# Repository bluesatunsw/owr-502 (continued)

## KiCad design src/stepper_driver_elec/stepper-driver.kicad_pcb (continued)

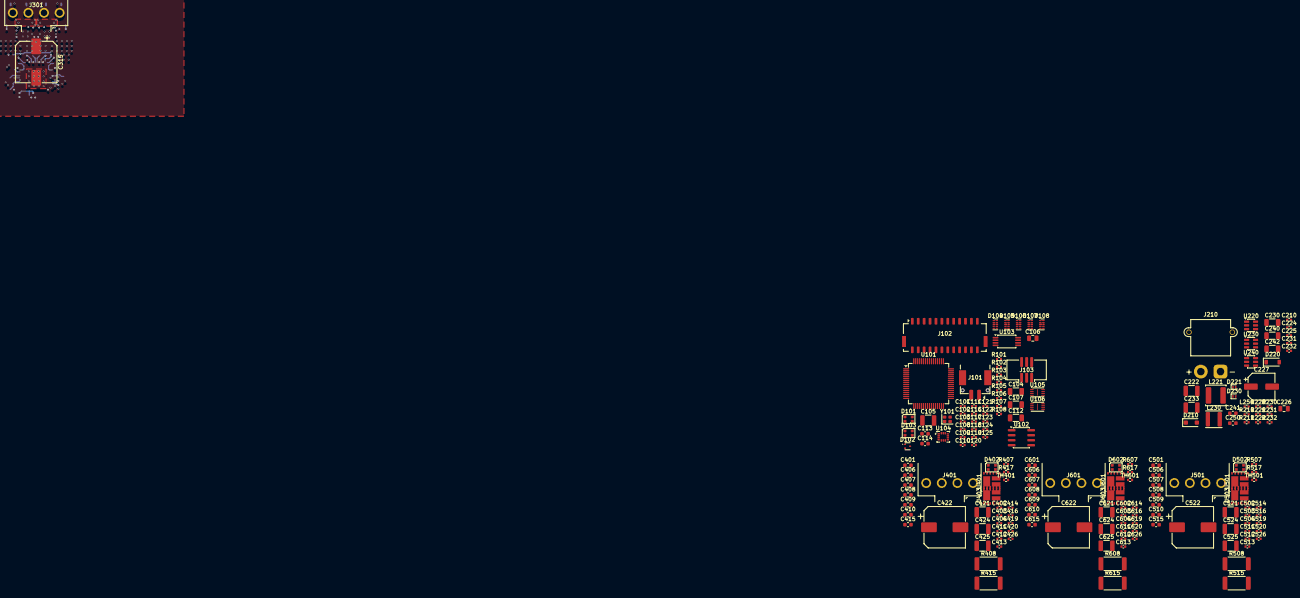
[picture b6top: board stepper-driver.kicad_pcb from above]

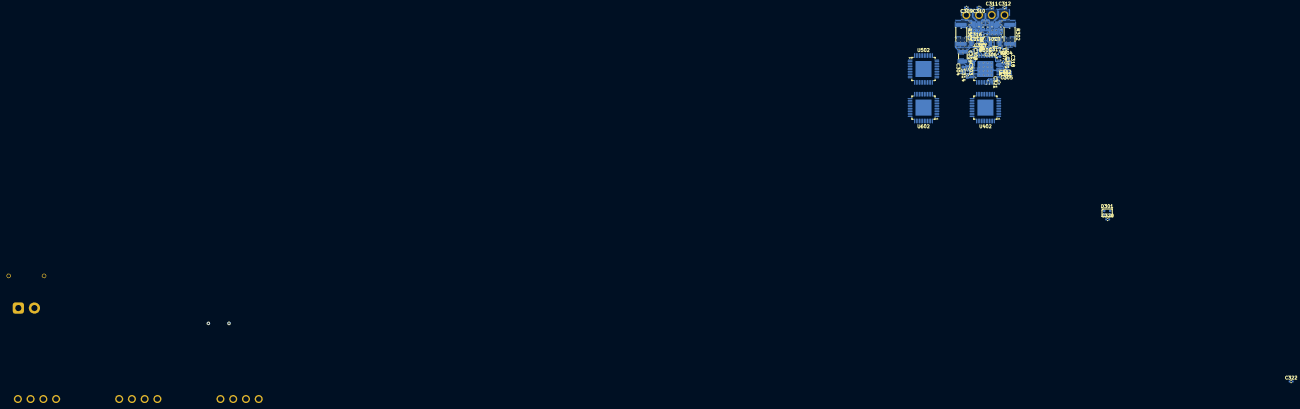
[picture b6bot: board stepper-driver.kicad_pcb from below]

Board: 6 copper layers, 211 parts (33 on the bottom side), 169 nets.

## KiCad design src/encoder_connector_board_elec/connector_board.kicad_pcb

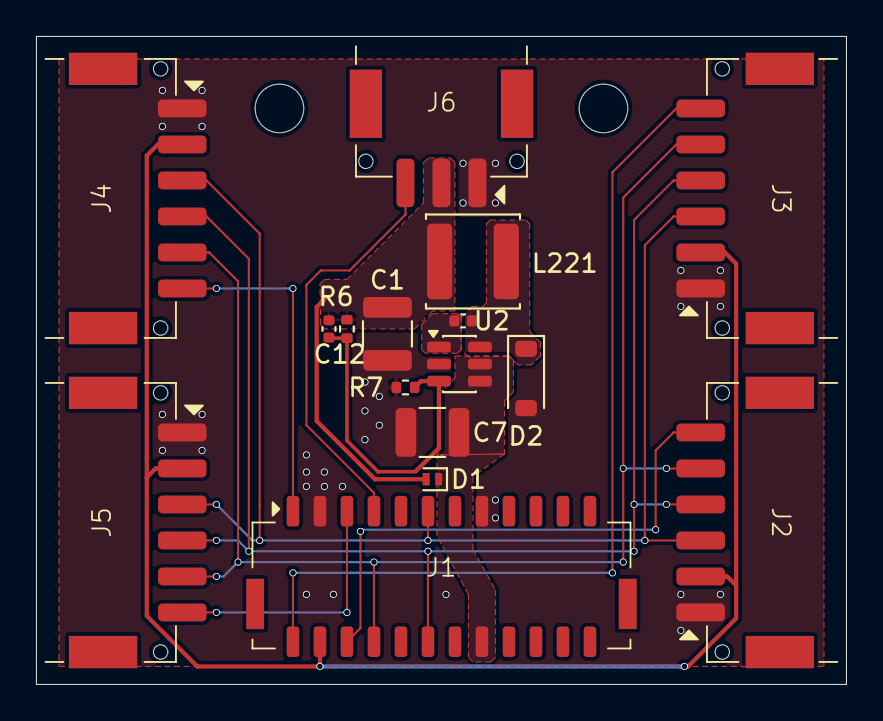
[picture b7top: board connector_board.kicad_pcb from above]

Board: 2 copper layers, 45.0 x 36.0 mm, 18 parts (0 on the bottom side), 15 nets.

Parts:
C1: 22u; C_1210_3225Metric
C7: 4u7; C_1210_3225Metric
C8: 100n; C_0402_1005Metric
C12: 33p; C_0402_1005Metric
D1: D_Schottky_Small; D_SOD-882
D2: D_Schottky_Small; D_SOD-123
H1, H2: M2.5; M2.5_Internal
J1: Conn_02x12_Odd_Even; BM24B-ZPDSS
J2, J3, J4, J5: Conn_01x06; SM06B-PASS
J6: Conn_01x03; SM03B-PASS
L221: 15u; L_Changjiang_FNR5040S
R6: 68k; R_0402_1005Metric
R7: 10k; R_0402_1005Metric
U2: MP2459GJ-Z-MS; TSOT-23-6

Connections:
+3V3: J1.4, J2.2, J3.2, J4.2, J5.2
+6V: C1.1, C12.1, D1.2 (A), J6.2, L221.1, R6.1
/BST: C8.1, U2.1 (BST)
/CLK: J1.8, J2.5, J3.5, J4.5, J5.5
/CS0: J1.1, J4.6
/CS1: J1.2, J3.6
/CS2: J1.5, J5.6
/CS3: J1.6, J2.6
/FB: C12.2, R6.2, R7.1, U2.3 (FB)
/MISO: J1.11, J2.3, J3.3, J4.3, J5.3
/MOSI: J1.12, J2.4, J3.4, J4.4, J5.4
/PWM: J1.7, J6.3
/SW: C8.2, D2.1 (K), L221.2, U2.6 (SW)
GND: C1.2, C7.2, D2.2 (A), J1.3, J1.15, J2.1, J3.1, J4.1, J5.1, J6.1, R7.2, U2.2 (GND)
VBUS: C7.1, D1.1 (K), J1.16, U2.4 (EN), U2.5 (IN)

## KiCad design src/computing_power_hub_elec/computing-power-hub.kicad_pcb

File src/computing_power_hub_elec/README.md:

# Computing Power Hub (CPH)

A device which provides and monitors regulated rails for communications (passive 24V POE), computing (19V), cameras (12V) and lighting (5V) devices. It complies with the common device specification 2025-04.

## Switching
Output to each rail can be switched.

## Monitoring
The output current and voltage of each rail is monitored.

## Rail Generation
The 19V, 12V and 5V rails are generated by TPS54560 buck regulators (designs documented with Excel spreadsheets from TI). Each of these rails should be able to deliver 5A. A TPS61175 regulator is used to generate the 24V 1A POE rail.

The high current 5V and 12V rails replace the regular rails in the common device specification.

## Connection
Power input for the CPH is provided via a male XT30 connector. The 19V and 12V rails are output to 2-pin JST VH headers, limited to 5A and 4A respectively. LED power is sent to four ARGB (WS2812) ports with a 3-pin JST PA header, limited to 1A each.

The board has a pair of RJ45 sockets, the Ethernet signal is passed between these ports with a POE power injected into one of the ports.

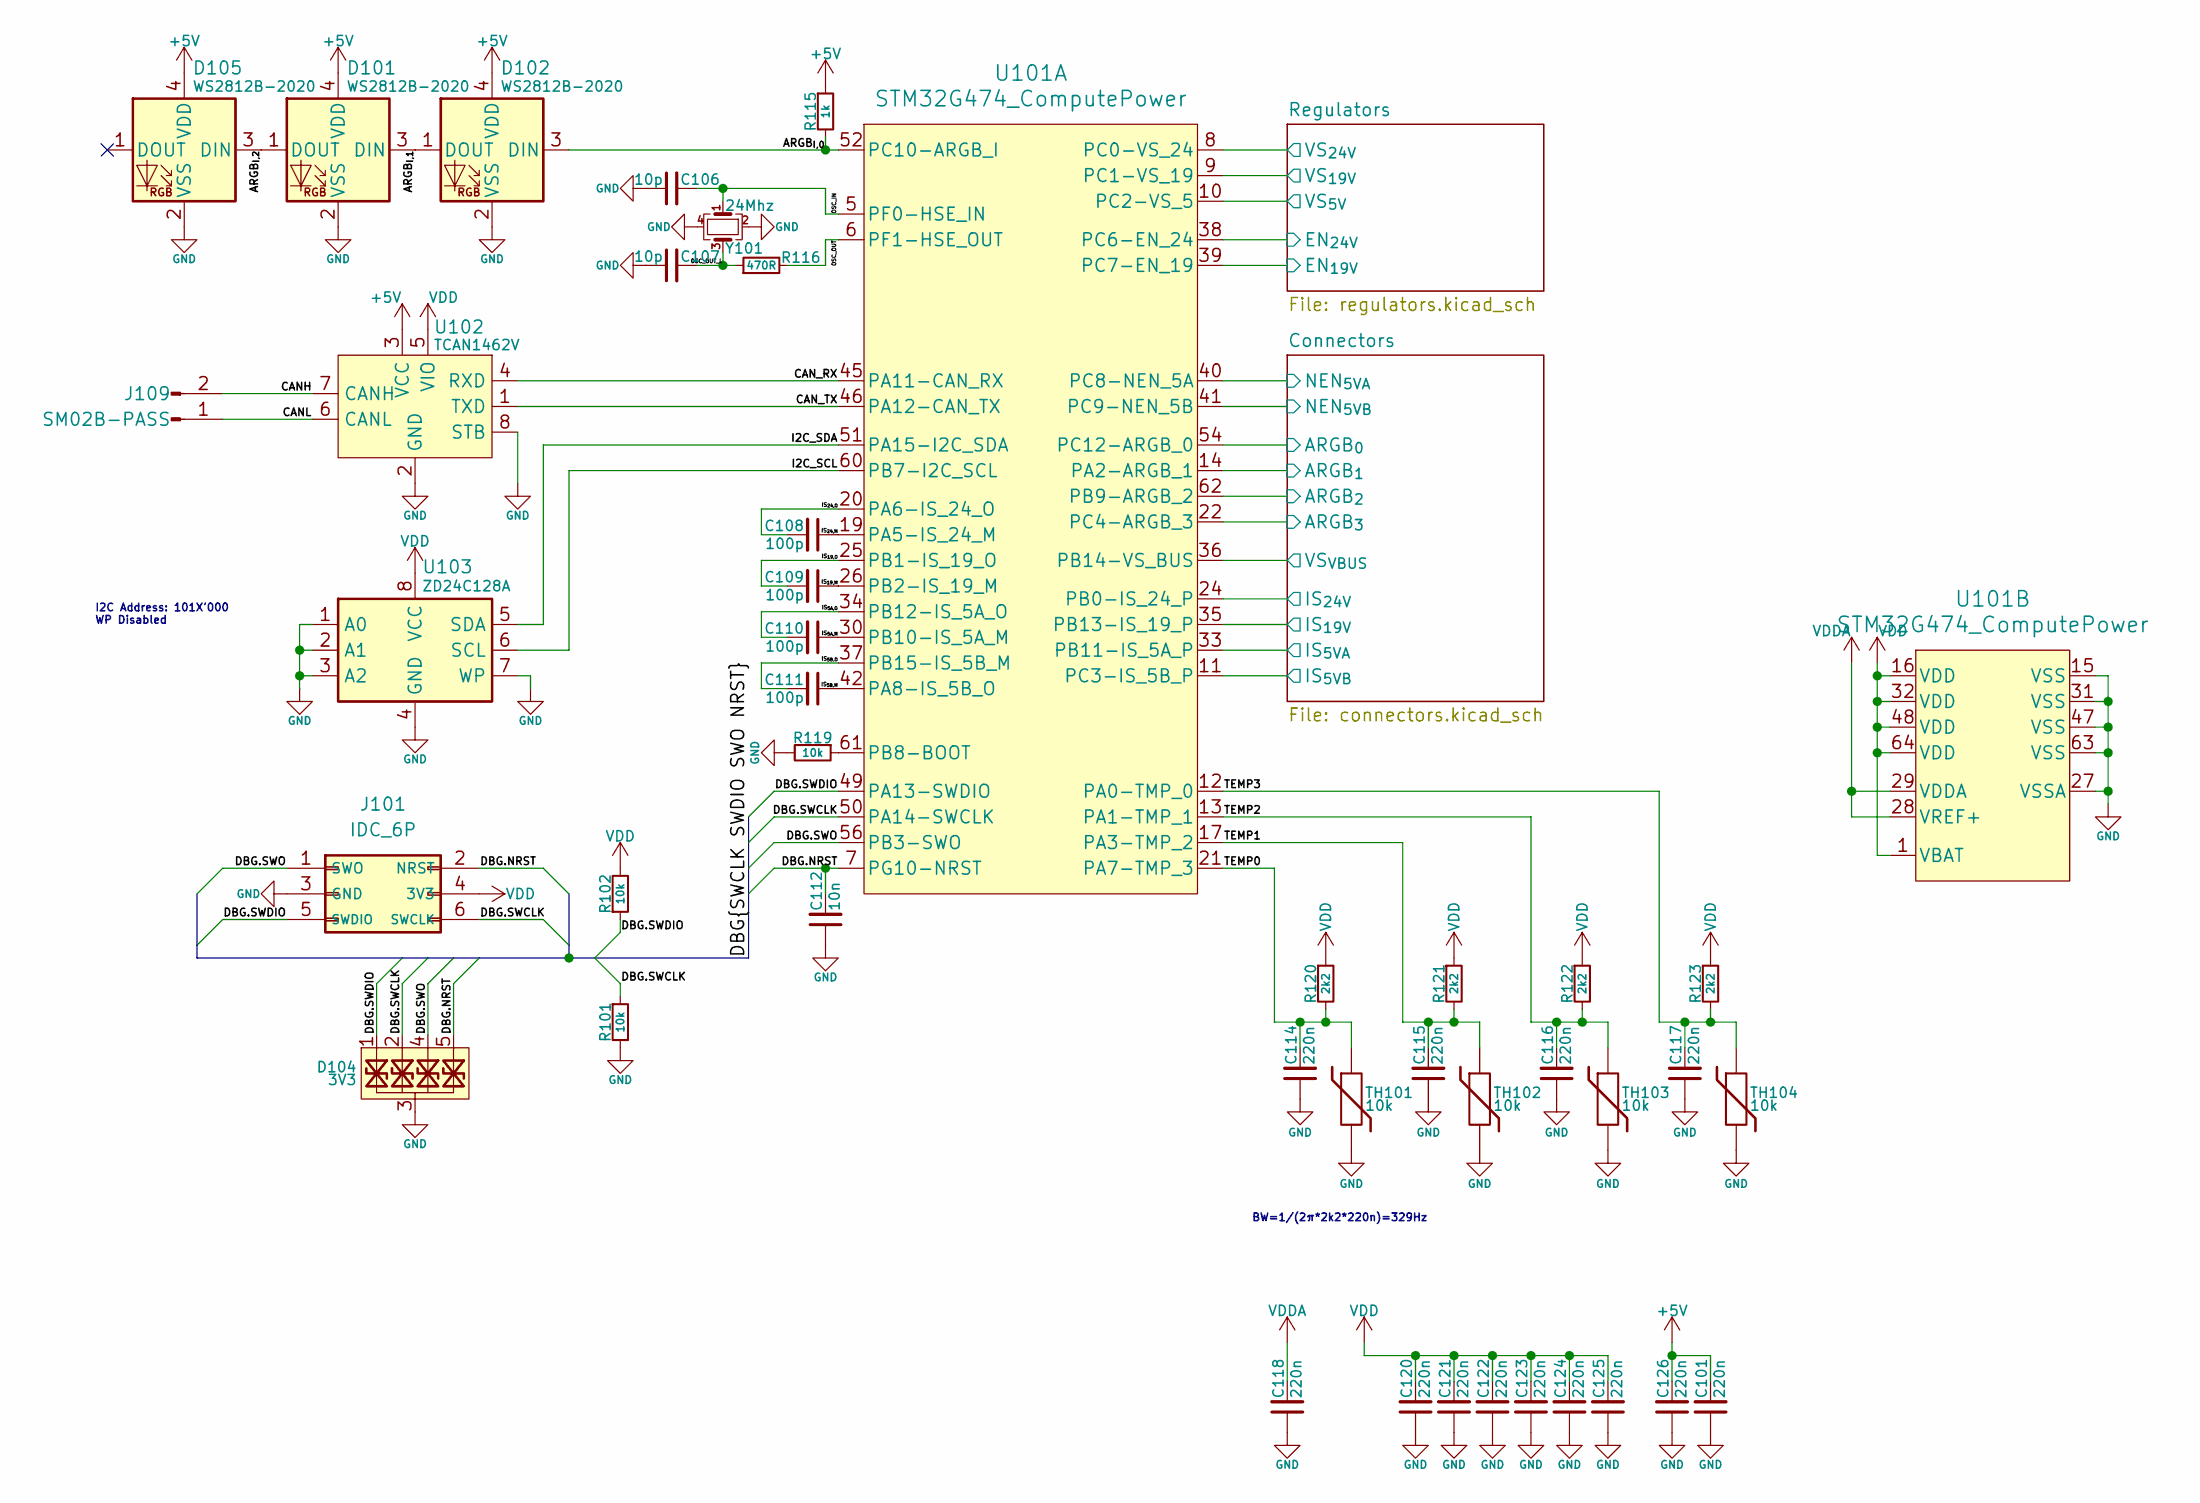
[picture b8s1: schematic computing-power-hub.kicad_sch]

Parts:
C101, C114, C115, C116, C117, C118, C120, C121, C122, C123, C124, C125, C126: 220n; C_0402_1005Metric
C106, C107: 10p; C_0402_1005Metric
C108, C109, C110, C111: 100p; C_0402_1005Metric
C112: 10n; C_0402_1005Metric
D101, D102, D105: WS2812B-2020
D104: 3V3; Diodes_UDFN-10_1x2.5mm_P0.5mm
J101: IDC_6P; IDC6
J109: SM02B-PASS
R101, R102, R119: 10k; R_0402_1005Metric
R115: 1k; R_0402_1005Metric
R116: 470R; R_0402_1005Metric
R120, R121, R122, R123: 2k2; R_0402_1005Metric
TH101, TH102, TH103, TH104: 10k; R_0402_1005Metric
U101: STM32G474_ComputePower; LQFP-64-0.5
U102: TCAN1462V; SOIC-8_3.9x4.9mm_P1.27mm
U103: ZD24C128A; TSSOP-8_4.4x3mm_P0.65mm
Y101: 24Mhz; Crystal_SMD_2016-4Pin_2.0x1.6mm

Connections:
+5V: C101.2, C126.2, D101.4 (VDD), D102.4 (VDD), D105.4 (VDD), R115.1, U102.3 (VCC); also elsewhere on the board
/ARGB_{I,0}: D102.3 (DIN), R115.2, U101.52 (PC10-ARGB_I)
/ARGB_{I,1}: D101.3 (DIN), D102.1 (DOUT)
/ARGB_{I,2}: D101.1 (DOUT), D105.3 (DIN)
/CANH: J109.2, U102.7 (CANH)
/CANL: J109.1, U102.6 (CANL)
/CAN_RX: U101.45 (PA11-CAN_RX), U102.4 (RXD)
/CAN_TX: U101.46 (PA12-CAN_TX), U102.1 (TXD)
/Connectors/ARGB_{0}: U101.54 (PC12-ARGB_0); also elsewhere on the board
/Connectors/ARGB_{1}: U101.14 (PA2-ARGB_1); also elsewhere on the board
/Connectors/ARGB_{2}: U101.62 (PB9-ARGB_2); also elsewhere on the board
/Connectors/ARGB_{3}: U101.22 (PC4-ARGB_3); also elsewhere on the board
/Connectors/IS_{5VA}: U101.33 (PB11-IS_5A_P); also elsewhere on the board
/Connectors/IS_{5VB}: U101.11 (PC3-IS_5B_P); also elsewhere on the board
/Connectors/IS_{19V}: U101.35 (PB13-IS_19_P); also elsewhere on the board
/Connectors/IS_{24V}: U101.24 (PB0-IS_24_P); also elsewhere on the board
/Connectors/NEN_{5VA}: U101.40 (PC8-NEN_5A); also elsewhere on the board
/Connectors/NEN_{5VB}: U101.41 (PC9-NEN_5B); also elsewhere on the board
/Connectors/VS_{VBUS}: U101.36 (PB14-VS_BUS); also elsewhere on the board
/DBG.NRST: C112.2, D104.5, D104.6, J101.2 (NRST), U101.7 (PG10-NRST)
/DBG.SWCLK: D104.2, D104.9, J101.6 (SWCLK), R101.1, U101.50 (PA14-SWCLK)
/DBG.SWDIO: D104.1, D104.10, J101.5 (SWDIO), R102.1, U101.49 (PA13-SWDIO)
/DBG.SWO: D104.4, D104.7, J101.1 (SWO), U101.56 (PB3-SWO)
/I2C_SCL: U101.60 (PB7-I2C_SCL), U103.6 (SCL)
/I2C_SDA: U101.51 (PA15-I2C_SDA), U103.5 (SDA)
/IS_{5A,M}: C110.1, U101.30 (PB10-IS_5A_M)
/IS_{5A,O}: C110.2, U101.34 (PB12-IS_5A_O)
/IS_{5B,M}: C111.1, U101.42 (PA8-IS_5B_O)
/IS_{5B,O}: C111.2, U101.37 (PB15-IS_5B_M)
/IS_{19,M}: C109.1, U101.26 (PB2-IS_19_M)
/IS_{19,O}: C109.2, U101.25 (PB1-IS_19_O)
/IS_{24,M}: C108.1, U101.19 (PA5-IS_24_M)
/IS_{24,O}: C108.2, U101.20 (PA6-IS_24_O)
/OSC_IN: C106.2, U101.5 (PF0-HSE_IN), Y101.1
/OSC_OUT: R116.2, U101.6 (PF1-HSE_OUT)
/OSC_OUT_L: C107.2, R116.1, Y101.3
/Regulators/EN_{19V}: U101.39 (PC7-EN_19); also elsewhere on the board
/Regulators/EN_{24V}: U101.38 (PC6-EN_24); also elsewhere on the board
/Regulators/VS_{5V}: U101.10 (PC2-VS_5); also elsewhere on the board
/Regulators/VS_{19V}: U101.9 (PC1-VS_19); also elsewhere on the board
/Regulators/VS_{24V}: U101.8 (PC0-VS_24); also elsewhere on the board
/TEMP0: C114.2, R120.2, TH101.1, U101.21 (PA7-TMP_3)
/TEMP1: C115.2, R121.2, TH102.1, U101.17 (PA3-TMP_2)
/TEMP2: C116.2, R122.2, TH103.1, U101.13 (PA1-TMP_1)
/TEMP3: C117.2, R123.2, TH104.1, U101.12 (PA0-TMP_0)
GND: C101.1, C106.1, C107.1, C112.1, C114.1, C115.1, C116.1, C117.1, C118.1, C120.1, C121.1, C122.1, C123.1, C124.1, C125.1, C126.1, D101.2 (VSS), D102.2 (VSS), D104.3, D104.8, D105.2 (VSS), J101.3 (GND), R101.2, R119.2, TH101.2, TH102.2, TH103.2, TH104.2, U101.15 (VSS), U101.27 (VSSA), U101.31 (VSS), U101.47 (VSS), U101.63 (VSS), U102.2 (GND), U102.8 (STB), U102.9 (EP), U103.1 (A0), U103.2 (A1), U103.3 (A2), U103.4 (GND), U103.7 (WP), Y101.2, Y101.4; also elsewhere on the board
unnamed: R119.1, U101.61 (PB8-BOOT)
VDD: C120.2, C121.2, C122.2, C123.2, C124.2, C125.2, J101.4 (3V3), R102.2, R120.1, R121.1, R122.1, R123.1, U101.1 (VBAT), U101.16 (VDD), U101.32 (VDD), U101.48 (VDD), U101.64 (VDD), U102.5 (VIO), U103.8 (VCC); also elsewhere on the board
VDDA: C118.2, U101.28 (VREF+), U101.29 (VDDA); also elsewhere on the board

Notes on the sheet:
I2C Address: 101X'000 WP Disabled
BW=1/(2π*2k2*220n)=329Hz

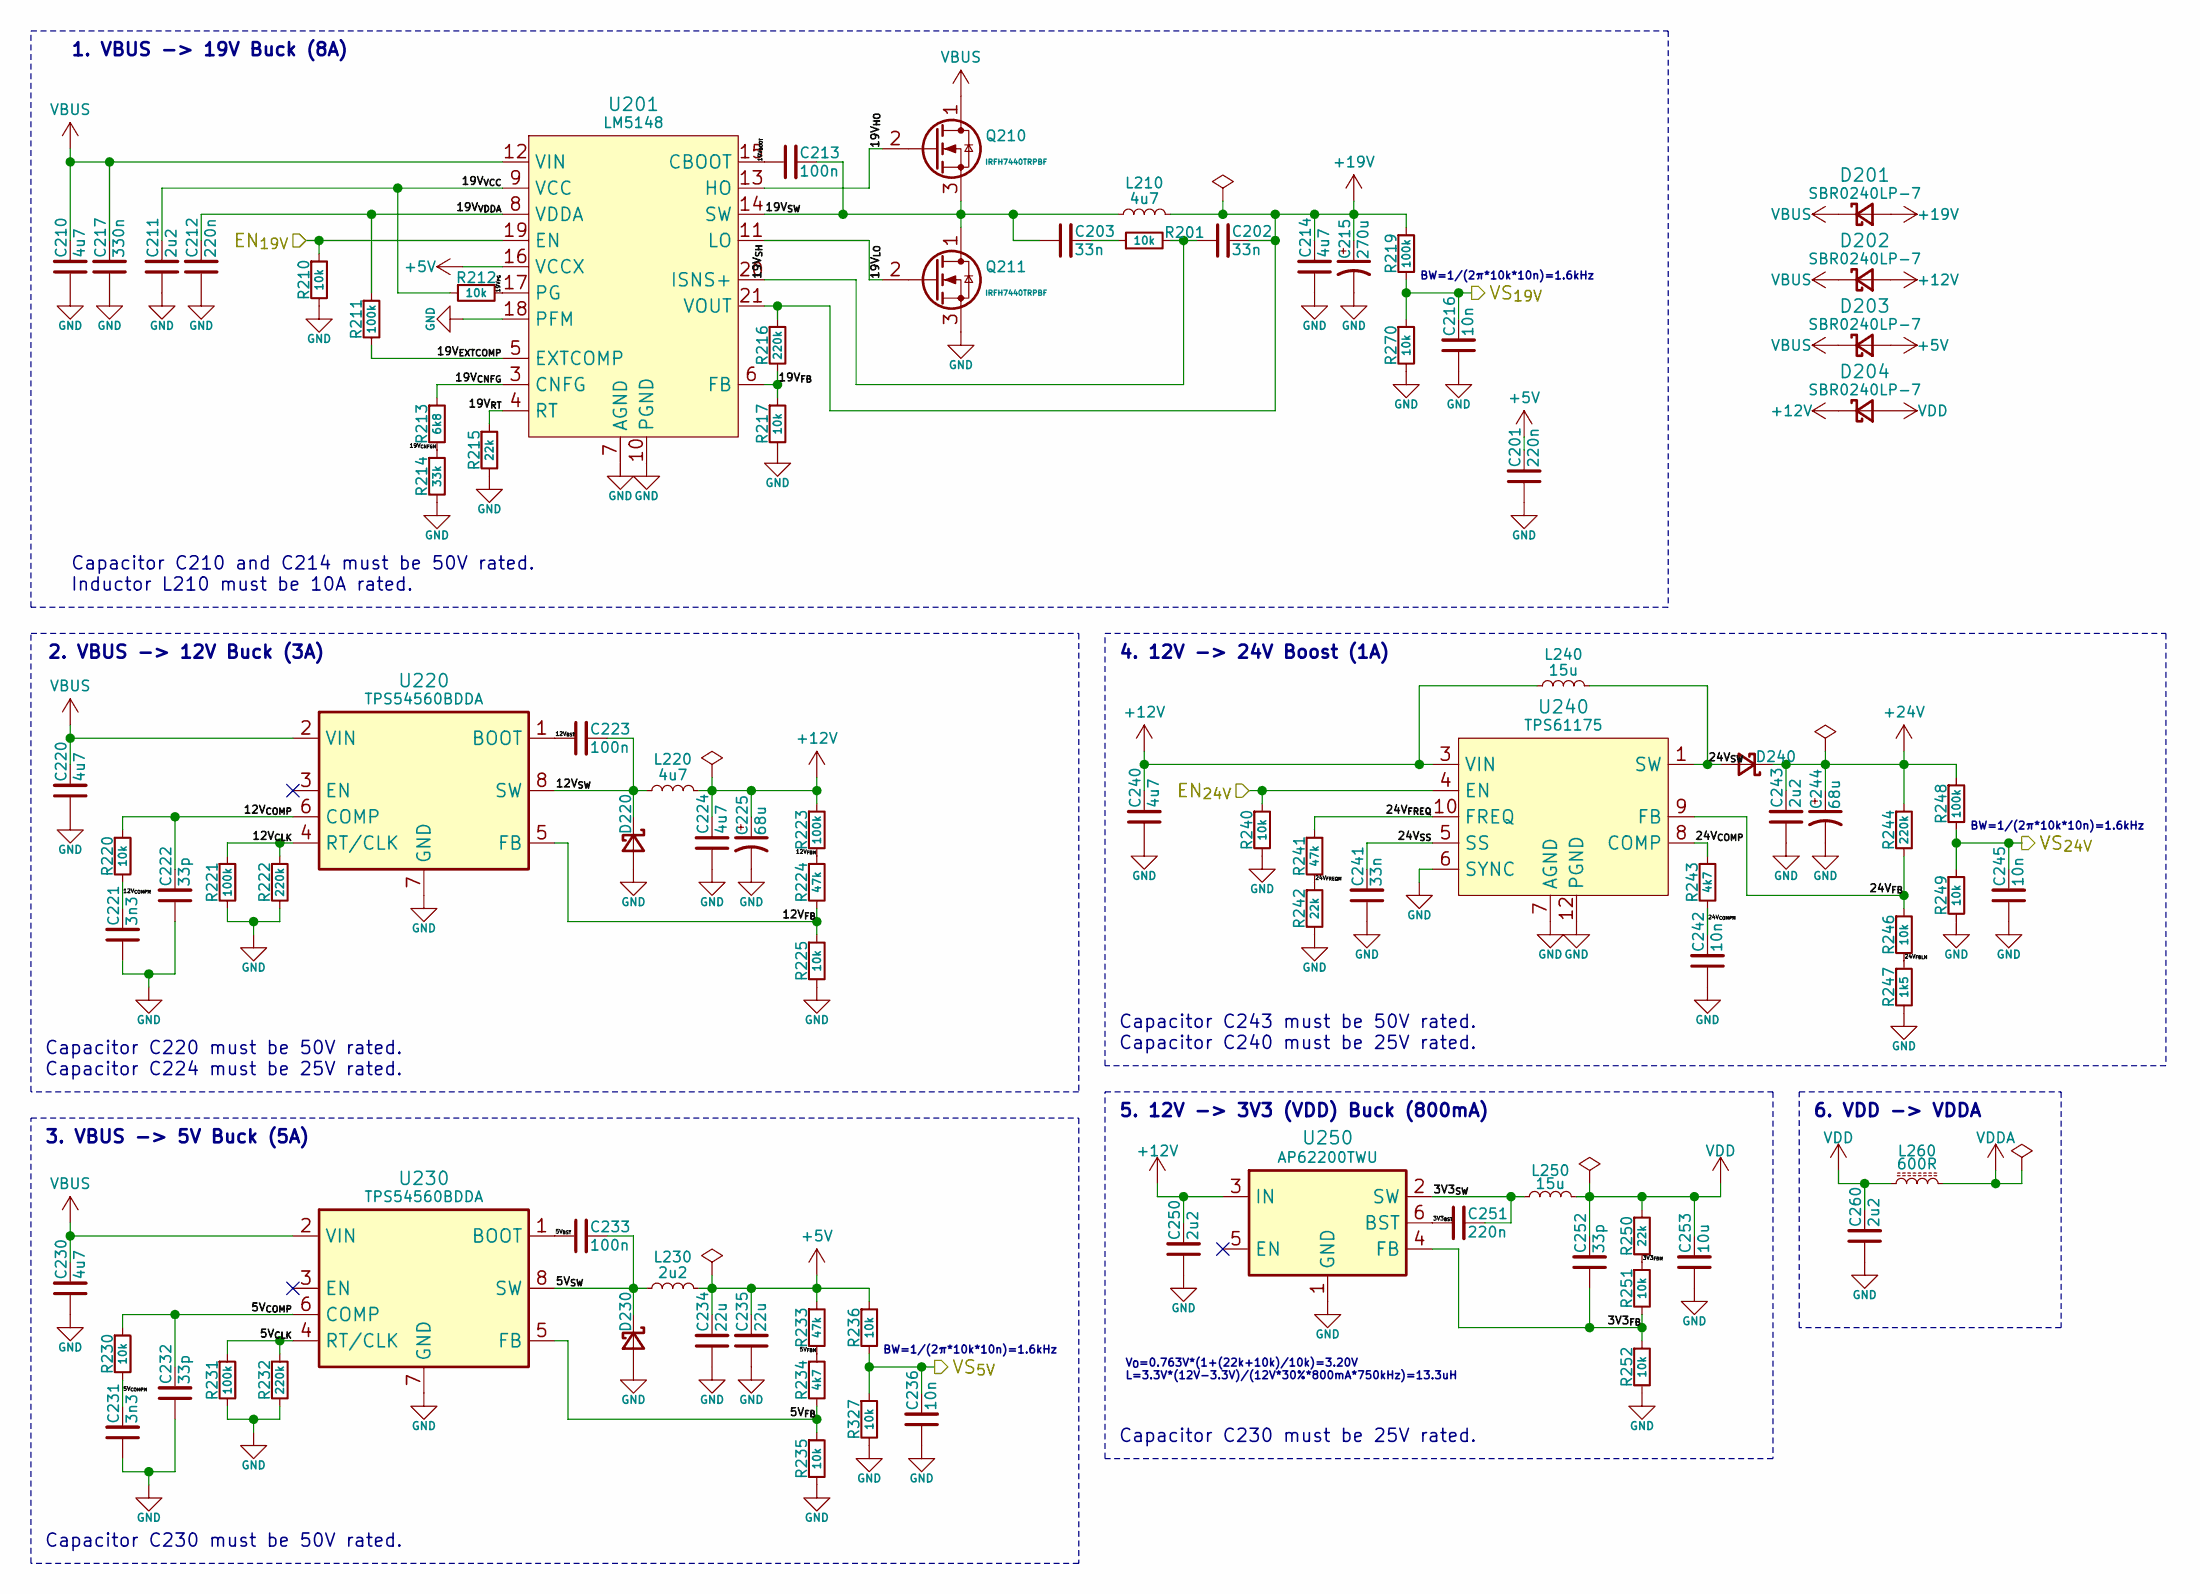
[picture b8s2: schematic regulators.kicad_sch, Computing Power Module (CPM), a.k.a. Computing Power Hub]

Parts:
C201, C212, C251: 220n; C_0402_1005Metric
C202, C203, C241: 33n; C_0402_1005Metric
C210, C214, C220, C230: 4u7; C_1210_3225Metric
C211, C260: 2u2; C_0603_1608Metric
C213, C223, C233: 100n; C_0402_1005Metric
C215: 270u; CP_Elec_10x10
C216, C236, C242, C245: 10n; C_0402_1005Metric
C217: 330n; C_0805_2012Metric
C221, C231: 3n3; C_0402_1005Metric
C222, C232, C252: 33p; C_0402_1005Metric
C224, C240: 4u7; C_1206_3216Metric
C225, C244: 68u; CP_Elec_6.3x7.7
C234, C235: 22u; C_1210_3225Metric
C243, C250: 2u2; C_1206_3216Metric
C253: 10u; C_1210_3225Metric
D201, D202, D203, D204: SBR0240LP-7; D_SOD-882
D220, D230, D240: D_Schottky_Small; D_SMA
L210: 4u7; L_Changjiang_FXL1360
L220: 4u7; L_Changjiang_FNR4020S
L230: 2u2; L_Changjiang_FXL0630
L240, L250: 15u; L_Changjiang_FNR5040S
L260: 600R; R_0402_1005Metric
Q210, Q211: IRFH7440TRPBF; PQFN_5x6mm_E_DGS
R201, R210, R212, R217, R220, R225, R230, R235, R236, R240, R246, R249, R251, R252, R270, R327: 10k; R_0402_1005Metric
R211, R219, R221, R223, R231, R248: 100k; R_0402_1005Metric
R213: 6k8; R_0402_1005Metric
R214: 33k; R_0402_1005Metric
R215, R242, R250: 22k; R_0402_1005Metric
R216, R222, R232, R244: 220k; R_0402_1005Metric
R224, R233, R241: 47k; R_0402_1005Metric
R234, R243: 4k7; R_0402_1005Metric
R247: 1k5; R_0402_1005Metric
U201: LM5148; RGY0024E-MFG
U220, U230: TPS54560BDDA; SOIC-8-1EP_3.9x4.9mm_P1.27mm_EP2.41x3.3mm
U240: TPS61175; PowerPAD_HTSSOP-14_4.4x5.0-0.65-EP
U250: AP62200TWU; TSOT-23-6

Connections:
+5V: C201.2, C234.2, C235.2, D203.2 (A), L230.2, R233.1, R236.1, U201.16 (VCCX); also elsewhere on the board
+12V: C224.2, C225.1, C240.2, C250.2, D202.2 (A), D204.1 (K), L220.2, L240.1, R223.1, U240.3 (VIN), U250.3 (IN); also elsewhere on the board
+19V: C202.2, C214.2, C215.1, D201.2 (A), L210.2, R216.1, R219.1, U201.21 (VOUT); also elsewhere on the board
+24V: C243.2, C244.1, D240.1 (K), R244.1, R248.1; also elsewhere on the board
/Regulators/3V3_{BST}: C251.1, U250.6 (BST)
/Regulators/3V3_{FBM}: R250.2, R251.1
/Regulators/3V3_{FB}: C252.1, R251.2, R252.1, U250.4 (FB)
/Regulators/3V3_{SW}: C251.2, L250.1, U250.2 (SW)
/Regulators/5V_{BST}: C233.1, U230.1 (BOOT)
/Regulators/5V_{CLK}: R231.1, R232.1, U230.4 (RT/CLK)
/Regulators/5V_{COMPM}: C231.2, R230.2
/Regulators/5V_{COMP}: C232.2, R230.1, U230.6 (COMP)
/Regulators/5V_{FBM}: R233.2, R234.1
/Regulators/5V_{FB}: R234.2, R235.1, U230.5 (FB)
/Regulators/5V_{SW}: C233.2, D230.1 (K), L230.1, U230.8 (SW)
/Regulators/12V_{BST}: C223.1, U220.1 (BOOT)
/Regulators/12V_{CLK}: R221.1, R222.1, U220.4 (RT/CLK)
/Regulators/12V_{COMPM}: C221.2, R220.2
/Regulators/12V_{COMP}: C222.2, R220.1, U220.6 (COMP)
/Regulators/12V_{FBM}: R223.2, R224.1
/Regulators/12V_{FB}: R224.2, R225.1, U220.5 (FB)
/Regulators/12V_{SW}: C223.2, D220.1 (K), L220.1, U220.8 (SW)
/Regulators/19V_{BOOT}: C213.1, U201.15 (CBOOT)
/Regulators/19V_{CNFGM}: R213.2, R214.1
/Regulators/19V_{CNFG}: R213.1, U201.3 (CNFG)
/Regulators/19V_{EXTCOMP}: R211.2, U201.5 (EXTCOMP)
/Regulators/19V_{FB}: R216.2, R217.1, U201.6 (FB)
/Regulators/19V_{HO}: Q210.2 (G), U201.13 (HO)
/Regulators/19V_{LO}: Q211.2 (G), U201.11 (LO)
/Regulators/19V_{PG}: R212.2, U201.17 (PG)
/Regulators/19V_{RT}: R215.1, U201.4 (RT)
/Regulators/19V_{SH}: C202.1, R201.2, U201.20 (ISNS+)
/Regulators/19V_{SW}: C203.1, C213.2, L210.1, Q210.3 (S), Q211.1 (D), U201.14 (SW)
/Regulators/19V_{VCC}: C211.2, R212.1, U201.9 (VCC)
/Regulators/19V_{VDDA}: C212.2, R211.1, U201.8 (VDDA)
/Regulators/24V_{COMPM}: C242.2, R243.2
/Regulators/24V_{COMP}: R243.1, U240.8 (COMP)
/Regulators/24V_{FBLM}: R246.2, R247.1
/Regulators/24V_{FB}: R244.2, R246.1, U240.9 (FB)
/Regulators/24V_{FREQM}: R241.2, R242.1
/Regulators/24V_{FREQ}: R241.1, U240.10 (FREQ)
/Regulators/24V_{SS}: C241.2, U240.5 (SS)
/Regulators/24V_{SW}: D240.2 (A), L240.2, U240.1 (SW), U240.2 (SW)
/Regulators/EN_{19V}: R210.1, U201.19 (EN); also elsewhere on the board
/Regulators/EN_{24V}: R240.1, U240.4 (EN); also elsewhere on the board
/Regulators/VS_{5V}: C236.2, R236.2, R327.1; also elsewhere on the board
/Regulators/VS_{19V}: C216.2, R219.2, R270.1; also elsewhere on the board
/Regulators/VS_{24V}: C245.2, R248.2, R249.1; also elsewhere on the board
GND: C201.1, C210.1, C211.1, C212.1, C214.1, C215.2, C216.1, C217.1, C220.1, C221.1, C222.1, C224.1, C225.2, C230.1, C231.1, C232.1, C234.1, C235.1, C236.1, C240.1, C241.1, C242.1, C243.1, C244.2, C245.1, C250.1, C253.1, C260.1, D220.2 (A), D230.2 (A), Q211.3 (S), R210.2, R214.2, R215.2, R217.2, R221.2, R222.2, R225.2, R231.2, R232.2, R235.2, R240.2, R242.2, R247.2, R249.2, R252.2, R270.2, R327.2, U201.1 (NC), U201.2 (NC), U201.7 (AGND), U201.10 (PGND), U201.18 (PFM), U201.22 (NC), U201.23 (NC), U201.24 (NC), U201.25 (NC), U220.7 (GND), U220.9 (GND), U230.7 (GND), U230.9 (GND), U240.6 (SYNC), U240.7 (AGND), U240.11 (NC), U240.12 (PGND), U240.13 (PGND), U240.14 (PGND), U240.15 (EP), U250.1 (GND); also elsewhere on the board
unnamed: C203.2, R201.1
VBUS: C210.2, C217.2, C220.2, C230.2, D201.1 (K), D202.1 (K), D203.1 (K), Q210.1 (D), U201.12 (VIN), U220.2 (VIN), U230.2 (VIN); also elsewhere on the board
VDD: C252.2, C253.2, C260.2, D204.2 (A), L250.2, L260.1, R250.1; also elsewhere on the board
VDDA: L260.2; also elsewhere on the board

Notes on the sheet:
Capacitor C220 must be 50V rated. Capacitor C224 must be 25V rated.
6. VDD -> VDDA
BW=1/(2π*10k*10n)=1.6kHz
2. VBUS -> 12V Buck (3A)
Capacitor C210 and C214 must be 50V rated. Inductor L210 must be 10A rated.
V_{O}=0.763V*(1+(22k+10k)/10k)=3.20V L=3.3V*(12V-3.3V)/(12V*30%*800mA*750kHz)=13.3uH
5. 12V -> 3V3 (VDD) Buck (800mA)
Capacitor C230 must be 25V rated.
Capacitor C230 must be 50V rated.
3. VBUS -> 5V Buck (5A)
1. VBUS -> 19V Buck (8A)
4. 12V -> 24V Boost (1A)
Capacitor C243 must be 50V rated. Capacitor C240 must be 25V rated.

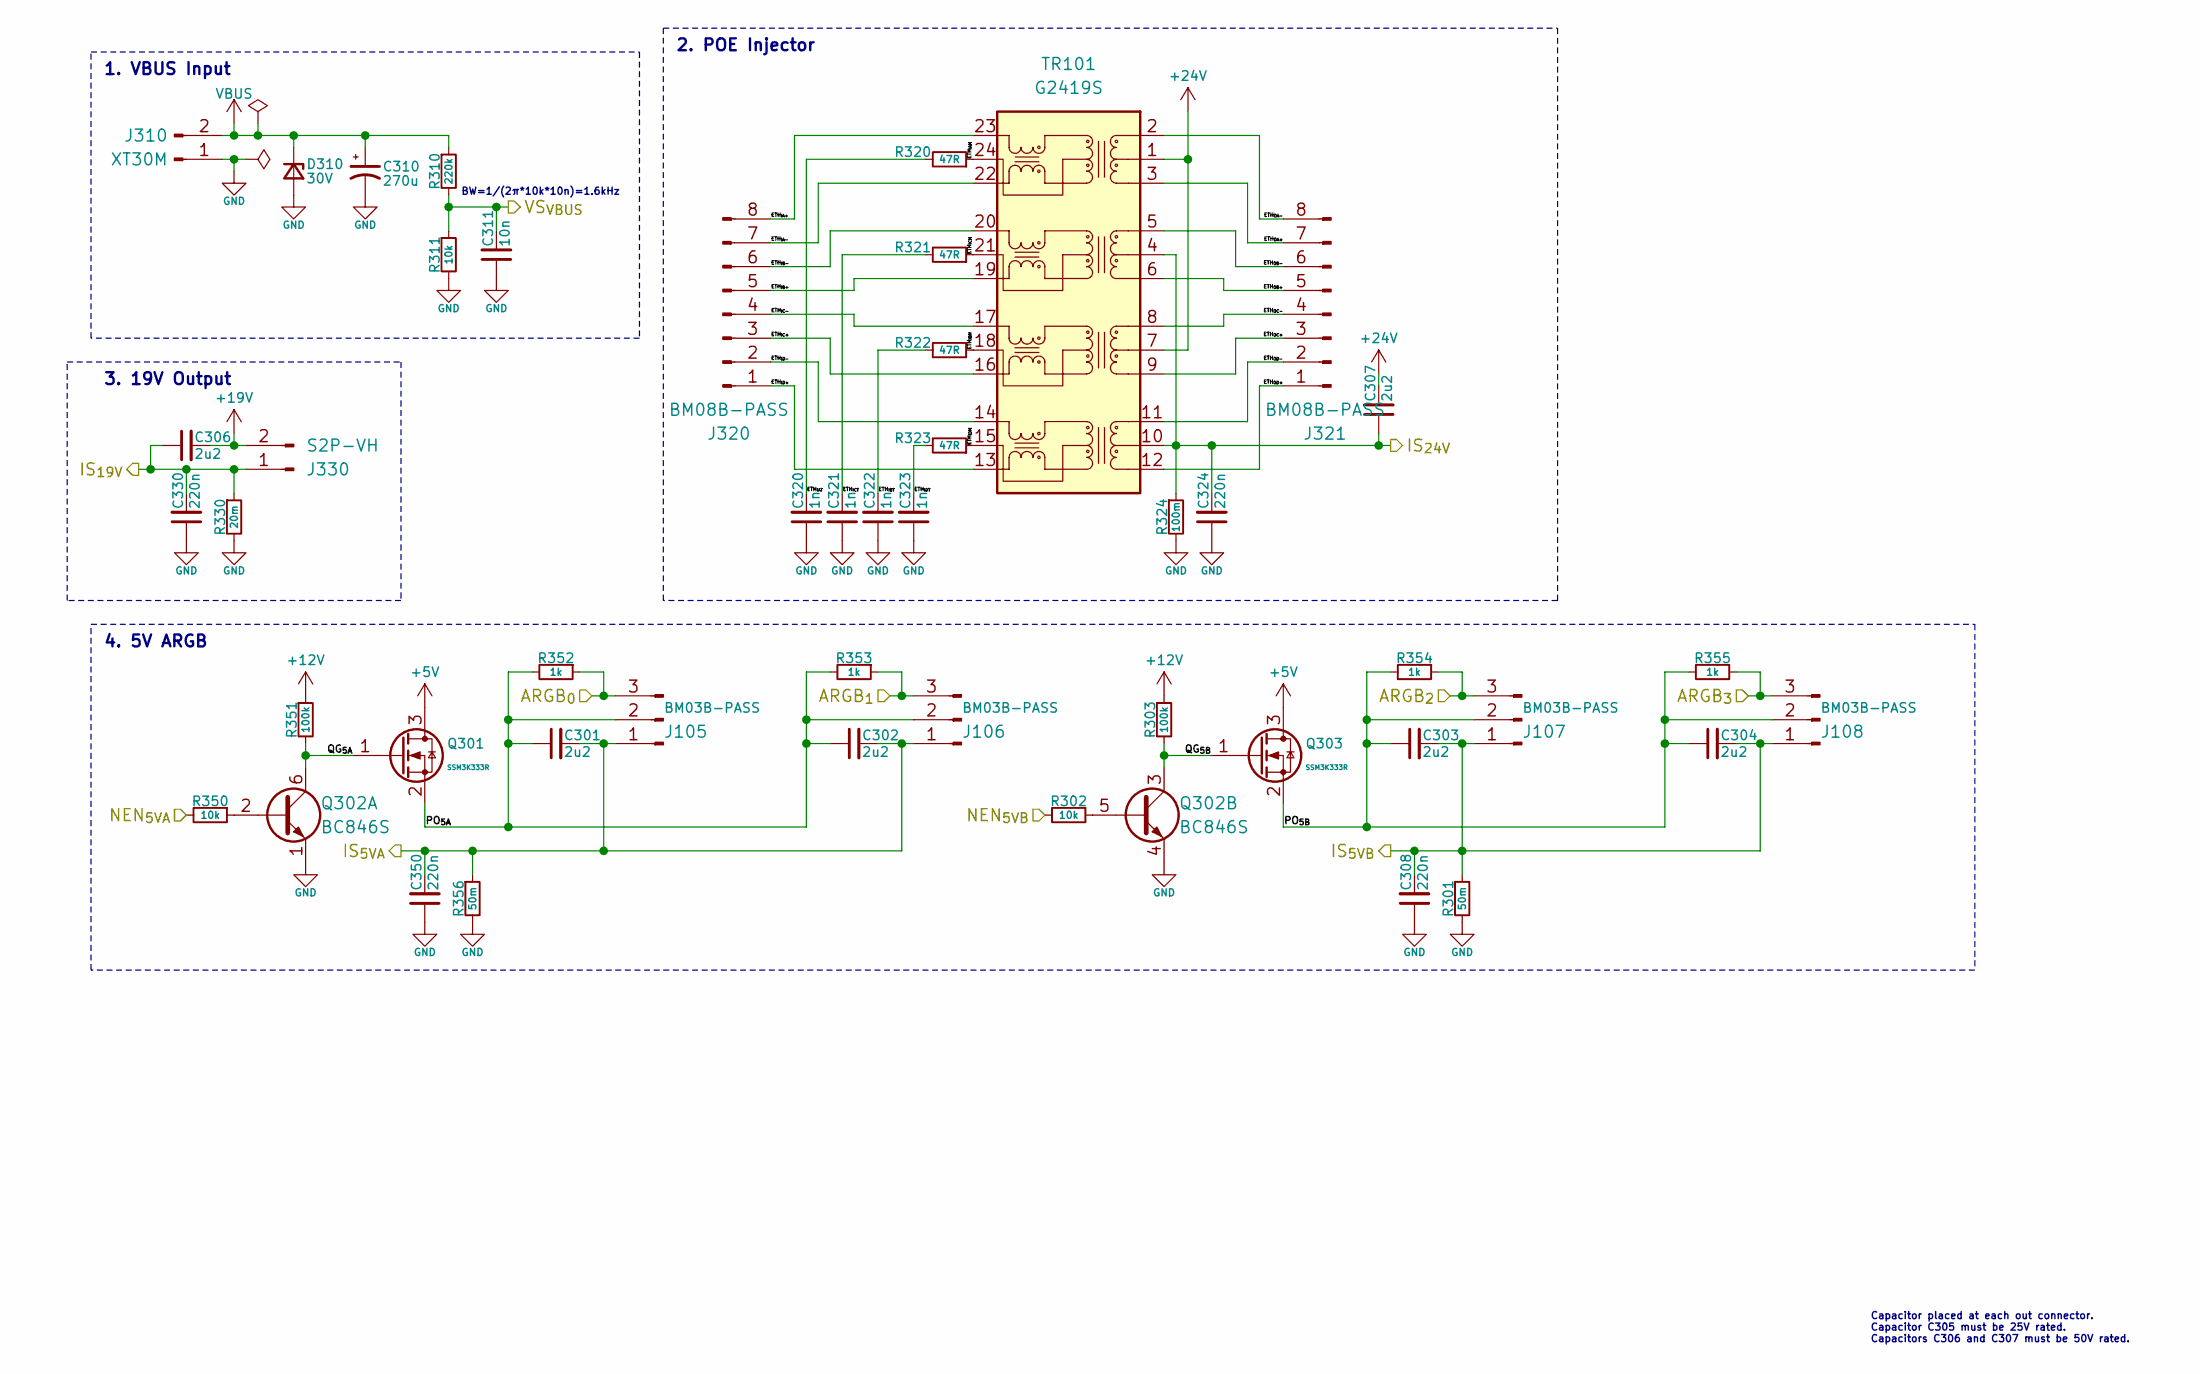
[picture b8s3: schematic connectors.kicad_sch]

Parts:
C301, C302, C303, C304: 2u2; C_0603_1608Metric
C306, C307: 2u2; C_1206_3216Metric
C308, C324, C330, C350: 220n; C_0402_1005Metric
C310: 270u; CP_Elec_10x10
C311: 10n; C_0402_1005Metric
C320, C321, C322, C323: 1n; C_0402_1005Metric
D310: 30V; D_SMF
J105, J106, J107, J108: BM03B-PASS
J310: XT30M; AMASS_XT30PW-M_1x02_P2.50mm_Horizontal
J320, J321: BM08B-PASS
J330: S2P-VH; B2P-VH
Q301, Q303: SSM3K333R; TSOT-23
Q302: BC846S; SOT-363
R301, R356: 50m; R_1206_3216Metric
R302, R311, R350: 10k; R_0402_1005Metric
R303, R351: 100k; R_0402_1005Metric
R310: 220k; R_0402_1005Metric
R320, R321, R322, R323: 47R; R_0402_1005Metric
R324: 100m; R_1206_3216Metric
R330: 20m; R_2512_6332Metric
R352, R353, R354, R355: 1k; R_0402_1005Metric
TR101: G2419S; Transformer_Ethernet

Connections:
+5V: Q301.3 (D), Q303.3 (D); also elsewhere on the board
+12V: R303.1, R351.1; also elsewhere on the board
+19V: C306.2, J330.2; also elsewhere on the board
+24V: C307.2, TR101.1 (CT), TR101.7 (CT); also elsewhere on the board
/Connectors/ARGB_{0}: J105.3, R352.1; also elsewhere on the board
/Connectors/ARGB_{1}: J106.3, R353.1; also elsewhere on the board
/Connectors/ARGB_{2}: J107.3, R354.1; also elsewhere on the board
/Connectors/ARGB_{3}: J108.3, R355.1; also elsewhere on the board
/Connectors/ETH_{IA+}: J320.8, TR101.23 (MX1+)
/Connectors/ETH_{IA-}: J320.7, TR101.22 (MX1-)
/Connectors/ETH_{IAM}: R320.1, TR101.24 (CT)
/Connectors/ETH_{IAT}: C320.2, R320.2
/Connectors/ETH_{IB+}: J320.5, TR101.19 (MX2-)
/Connectors/ETH_{IB-}: J320.6, TR101.20 (MX2+)
/Connectors/ETH_{IBM}: R322.1, TR101.18 (CT)
/Connectors/ETH_{IBT}: C322.2, R322.2
/Connectors/ETH_{IC+}: J320.3, TR101.16 (MX3-)
/Connectors/ETH_{IC-}: J320.4, TR101.17 (MX3+)
/Connectors/ETH_{ICM}: R321.1, TR101.21 (CT)
/Connectors/ETH_{ICT}: C321.2, R321.2
/Connectors/ETH_{ID+}: J320.1, TR101.13 (MX4-)
/Connectors/ETH_{ID-}: J320.2, TR101.14 (MX4+)
/Connectors/ETH_{IDM}: R323.1, TR101.15 (CT)
/Connectors/ETH_{IDT}: C323.2, R323.2
/Connectors/ETH_{OA+}: J321.7, TR101.3 (TD1-)
/Connectors/ETH_{OA-}: J321.8, TR101.2 (TD1+)
/Connectors/ETH_{OB+}: J321.5, TR101.6 (TD2-)
/Connectors/ETH_{OB-}: J321.6, TR101.5 (TD2+)
/Connectors/ETH_{OC+}: J321.3, TR101.9 (TD3-)
/Connectors/ETH_{OC-}: J321.4, TR101.8 (TD3+)
/Connectors/ETH_{OD+}: J321.1, TR101.12 (TD4-)
/Connectors/ETH_{OD-}: J321.2, TR101.11 (TD4+)
/Connectors/IS_{5VA}: C301.2, C302.2, C350.2, J105.1, J106.1, R356.1; also elsewhere on the board
/Connectors/IS_{5VB}: C303.2, C304.2, C308.2, J107.1, J108.1, R301.1; also elsewhere on the board
/Connectors/IS_{19V}: C306.1, C330.2, J330.1, R330.1; also elsewhere on the board
/Connectors/IS_{24V}: C307.1, C324.2, R324.1, TR101.4 (CT), TR101.10 (CT); also elsewhere on the board
/Connectors/NEN_{5VA}: R350.2; also elsewhere on the board
/Connectors/NEN_{5VB}: R302.2; also elsewhere on the board
/Connectors/PO_{5A}: C301.1, C302.1, J105.2, J106.2, Q301.2 (S), R352.2, R353.2
/Connectors/PO_{5B}: C303.1, C304.1, J107.2, J108.2, Q303.2 (S), R354.2, R355.2
/Connectors/QG_{5A}: Q301.1 (G), Q302.6 (C1), R351.2
/Connectors/QG_{5B}: Q302.3 (C2), Q303.1 (G), R303.2
/Connectors/VS_{VBUS}: C311.2, R310.2, R311.1; also elsewhere on the board
GND: C308.1, C310.2, C311.1, C320.1, C321.1, C322.1, C323.1, C324.1, C330.1, C350.1, D310.2 (A), J310.1, Q302.1 (E1), Q302.4 (E2), R301.2, R311.2, R324.2, R330.2, R356.2; also elsewhere on the board
unnamed: Q302.2 (B1), R350.1
unnamed: Q302.5 (B2), R302.1
VBUS: C310.1, D310.1 (K), J310.2, R310.1; also elsewhere on the board

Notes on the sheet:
Capacitor placed at each out connector. Capacitor C305 must be 25V rated. Capacitors C306 and C307 must be 50V rated.
1. VBUS Input
3. 19V Output
BW=1/(2π*10k*10n)=1.6kHz
4. 5V ARGB
2. POE Injector
